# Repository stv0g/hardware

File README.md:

This repository contains several smaller PCB layouts for projects I've worked on.

For more information take a look at the README files in the particular subdirectories or search on my [blog](http://www.noteblok.net) for the projects.

## Author

Steffen Vogel <post@steffenvogel.de>

## License

All these files are released if not otherwise noted under the GNU General Public License:

Copyright (C) 2014 Steffen Vogel

This program is free software: you can redistribute it and/or modify
it under the terms of the GNU General Public License as published by
the Free Software Foundation, either version 3 of the License, or
(at your option) any later version.

This program is distributed in the hope that it will be useful,
but WITHOUT ANY WARRANTY; without even the implied warranty of
MERCHANTABILITY or FITNESS FOR A PARTICULAR PURPOSE.  See the
GNU General Public License for more details.

You should have received a copy of the GNU General Public License
along with this program.  If not, see <http://www.gnu.org/licenses/>.

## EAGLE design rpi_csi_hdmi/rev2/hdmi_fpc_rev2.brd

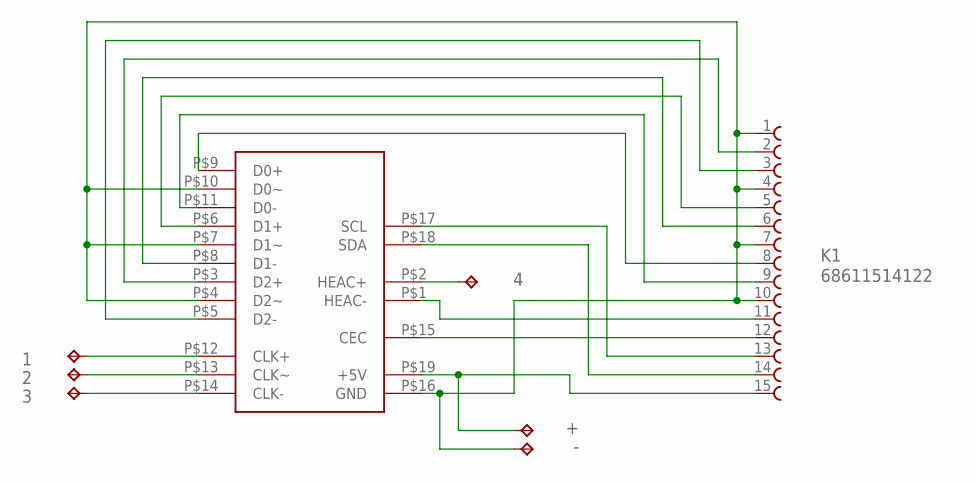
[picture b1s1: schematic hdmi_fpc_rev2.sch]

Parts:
1, 2, 3, 4: TPPAD1-13; P1-13
+: TPPAD1-13; P1-13
-: TPPAD1-13; P1-13
K1: 68611514122
U$1: HDMI_MICRO; MICRO_HDMI

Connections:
GND: -.TP, K1.1, K1.4, K1.7, K1.10, U$1.P$4 (D2~), U$1.P$7 (D1~), U$1.P$10 (D0~), U$1.P$16 (GND)
unnamed: K1.6, U$1.P$8 (D1-)
unnamed: 1.TP, U$1.P$12 (CLK+)
unnamed: K1.5, U$1.P$6 (D1+)
unnamed: K1.3, U$1.P$5 (D2-)
unnamed: K1.11, U$1.P$1 (HEAC-)
unnamed: K1.2, U$1.P$3 (D2+)
unnamed: K1.8, U$1.P$9 (D0+)
unnamed: 2.TP, U$1.P$13 (CLK~)
unnamed: K1.9, U$1.P$11 (D0-)
unnamed: K1.13, U$1.P$17 (SCL)
unnamed: K1.14, U$1.P$18 (SDA)
unnamed: +.TP, K1.15, U$1.P$19 (+5V)
unnamed: K1.12, U$1.P$15 (CEC)
unnamed: 3.TP, U$1.P$14 (CLK-)
unnamed: 4.TP, U$1.P$2 (HEAC+)

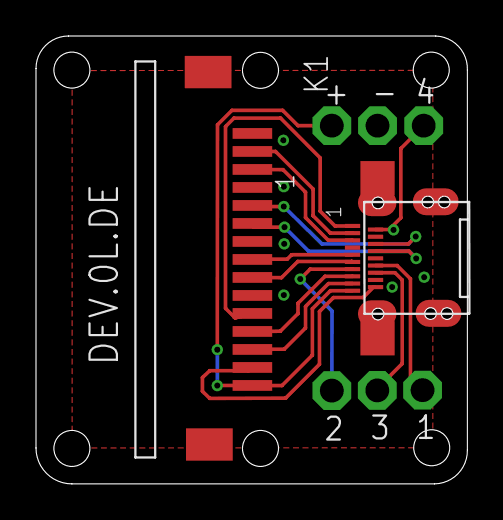
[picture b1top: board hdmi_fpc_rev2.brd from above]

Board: 2 copper layers, 24.0 x 24.9 mm, 8 parts (0 on the bottom side), 16 nets.

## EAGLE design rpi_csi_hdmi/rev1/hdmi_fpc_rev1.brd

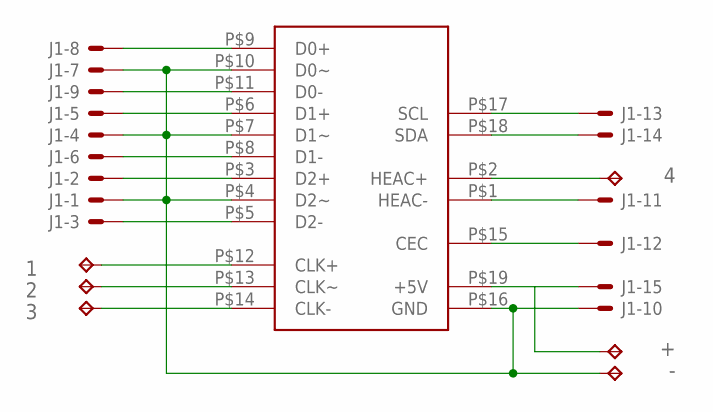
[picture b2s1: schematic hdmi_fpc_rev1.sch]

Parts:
1, 2, 3, 4: TPPAD1-13; P1-13
+: TPPAD1-13; P1-13
-: TPPAD1-13; P1-13
J1: XF2L-1535-1
U$1: HDMI_MICRO; MICRO_HDMI

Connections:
GND: -.TP, J1.1 (MSV), J1.4 (MS), J1.7 (MS), J1.10 (MS), U$1.P$4 (D2~), U$1.P$7 (D1~), U$1.P$10 (D0~), U$1.P$16 (GND)
unnamed: J1.6 (MS), U$1.P$8 (D1-)
unnamed: 1.TP, U$1.P$12 (CLK+)
unnamed: J1.5 (MS), U$1.P$6 (D1+)
unnamed: J1.3 (MS), U$1.P$5 (D2-)
unnamed: J1.11 (MS), U$1.P$1 (HEAC-)
unnamed: J1.2 (MS), U$1.P$3 (D2+)
unnamed: J1.8 (MS), U$1.P$9 (D0+)
unnamed: 2.TP, U$1.P$13 (CLK~)
unnamed: J1.9 (MS), U$1.P$11 (D0-)
unnamed: J1.13 (MS), U$1.P$17 (SCL)
unnamed: J1.14 (MS), U$1.P$18 (SDA)
unnamed: +.TP, J1.15 (MS), U$1.P$19 (+5V)
unnamed: J1.12 (MS), U$1.P$15 (CEC)
unnamed: 3.TP, U$1.P$14 (CLK-)
unnamed: 4.TP, U$1.P$2 (HEAC+)

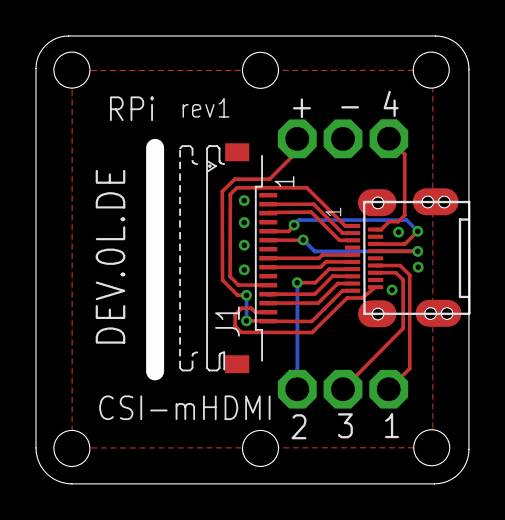
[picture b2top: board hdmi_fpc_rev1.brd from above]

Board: 2 copper layers, 23.1 x 23.9 mm, 8 parts (0 on the bottom side), 16 nets.

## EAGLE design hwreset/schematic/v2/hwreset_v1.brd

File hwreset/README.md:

# HWreset

'HWreset' is a little ATmega8 microcontroller which uses the V-USB software stack to connect to your PC.
Its equipped with two low voltage singaling relays to emulate your power and reset switches on a secondary SUT (system under test).

I use this little tool to speed up my compile & debug cycle for x86 os development with [MetalSVM] (http://www.lfbs.rwth-aachen.de/content/765)

## Hardware

You might want to use an existing [USBasp] (http://www.fischl.de/usbasp/) AVR Programmer and reflash it with the provided firmware. The USBasp is also based on the V-USB stack and has pretty much everything we need conserning the hardware.
The firmware is compatible with the USBasp pin assignments.

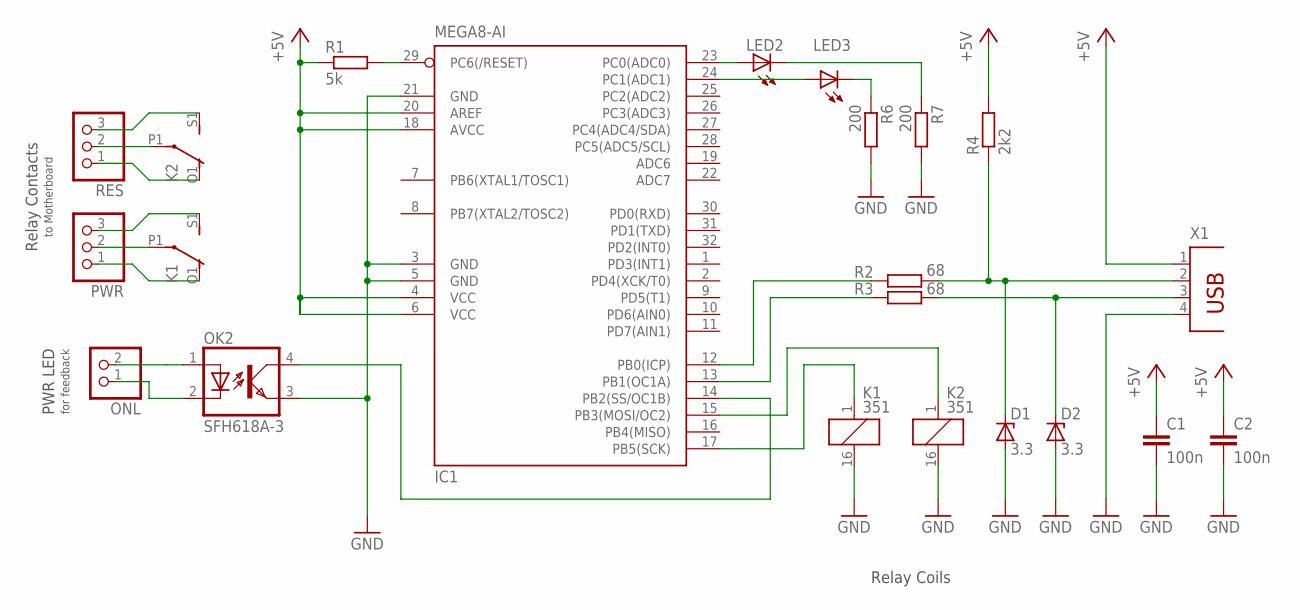
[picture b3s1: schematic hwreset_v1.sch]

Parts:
C1, C2: 100n; C025-025X050
D1, D2: 3.3; ZDIO-2.5
IC1: MEGA8-AI; TQFP32-08
K1, K2: 351
LED2, LED3: LED3MM
OK2: SFH618A-3; DIP4
ONL: PINHD-1X2; 1X02
PWR: PINHD-1X3; 1X03
R1: 5k; 0204V
R2, R3: 68; 0204V
R4: 2k2; 0204V
R6, R7: 200; 0204V
RES: PINHD-1X3; 1X03
X1: PN87520

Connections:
+5V: C1.1, C2.1, IC1.4 (VCC), IC1.6 (VCC), IC1.18 (AVCC), IC1.20 (AREF), R1.1, R4.2, X1.1
GND: C1.2, C2.2, D1.A, IC1.3 (GND), IC1.5 (GND), IC1.21 (GND), K1.16 (2), K2.16 (2), OK2.3 (EMIT), R6.2, R7.2, X1.4
unnamed: IC1.29 (PC6(/RESET)), R1.2
unnamed: IC1.17 (PB5(SCK)), K1.1
unnamed: K2.P1, RES.2
unnamed: IC1.12 (PB0(ICP)), R2.1
unnamed: IC1.13 (PB1(OC1A)), R3.1
unnamed: K1.P1, PWR.2
unnamed: D1.C, R2.2, R4.1, X1.2
unnamed: D2.C, R3.2, X1.3
unnamed: K1.O1 (O), PWR.1
unnamed: K1.S1 (S), PWR.3
unnamed: K2.O1 (O), RES.1
unnamed: K2.S1 (S), RES.3
unnamed: OK2.1 (A), ONL.2
unnamed: OK2.2 (C), ONL.1
unnamed: IC1.14 (PB2(SS/OC1B)), OK2.4 (COL)
unnamed: IC1.23 (PC0(ADC0)), LED2.A
unnamed: IC1.15 (PB3(MOSI/OC2)), K2.1
unnamed: IC1.24 (PC1(ADC1)), LED3.A
unnamed: LED2.K (C), R7.1
unnamed: LED3.K (C), R6.1

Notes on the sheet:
Relay Coils
Relay Contacts
to Motherboard
PWR LED
for feedback

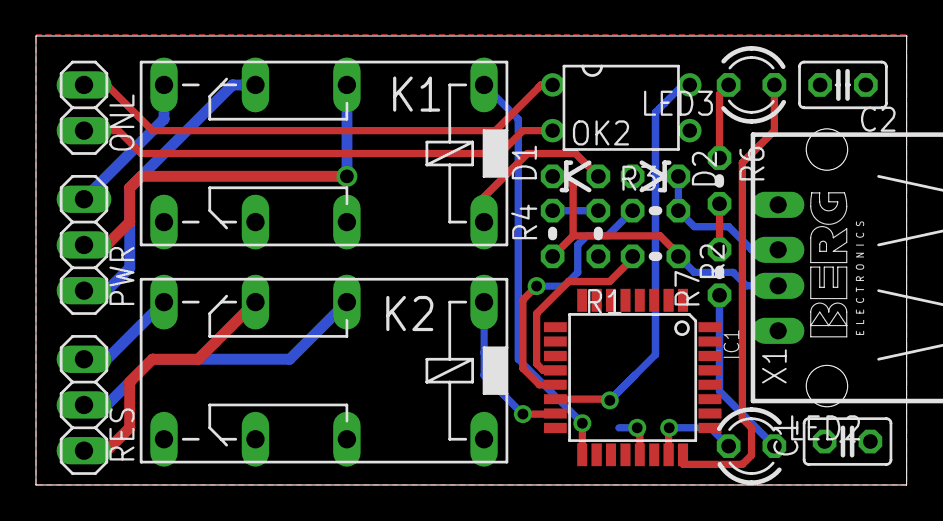
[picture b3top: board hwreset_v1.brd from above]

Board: 2 copper layers, 48.4 x 24.9 mm, 20 parts (0 on the bottom side), 22 nets.

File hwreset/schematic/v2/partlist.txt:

Partlist

Exported from untitled.sch at 18.01.14 01:03

EAGLE Version 6.1.0 Copyright (c) 1988-2012 CadSoft

Assembly variant: 

Part     Value          Device            Package      Library     Sheet

C1       100n           C-EU025-025X050   C025-025X050 rcl         1
C2       100n           C-EU025-025X050   C025-025X050 rcl         1
D1       3.3            ZENER-DIODEZD-2.5 ZDIO-2.5     diode       1
D2       3.3            ZENER-DIODEZD-2.5 ZDIO-2.5     diode       1
IC1      TINY22P        TINY22P           DIL08        atmel       1
K1       351            351               351          relay       1
K2       351            351               351          relay       1
LED1                    LED3MM            LED3MM       led         1
OK2      SFH618A-3      SFH618A-3         DIP4         optocoupler 1
ONL                     PINHD-1X2         1X02         pinhead     1
PWR                     PINHD-1X3         1X03         pinhead     1
R1       5k             R-EU_0204/2V      0204V        rcl         1
R2       68             R-EU_0204/2V      0204V        rcl         1
R3       68             R-EU_0204/2V      0204V        rcl         1
R4       2k2            R-EU_0204/2V      0204V        rcl         1
R5       200            R-EU_0204/2V      0204V        rcl         1
RES                     PINHD-1X3         1X03         pinhead     1
X1                      PN87520           PN87520      con-berg    1

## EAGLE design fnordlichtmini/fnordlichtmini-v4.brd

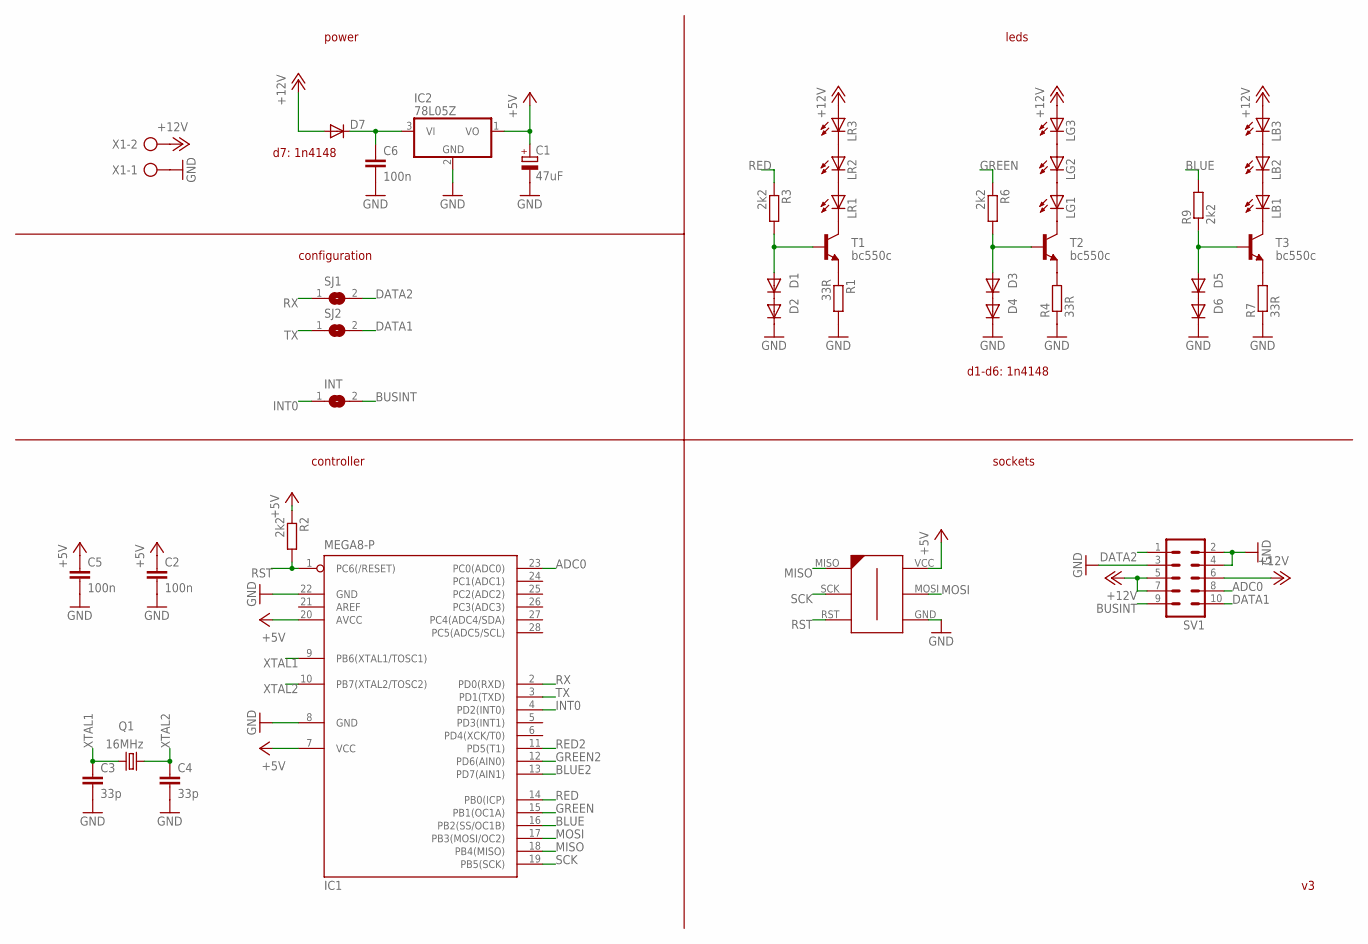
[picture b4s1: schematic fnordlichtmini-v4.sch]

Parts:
C1: 47uF; E2-5
C2, C5, C6: 100n; C025-024X044
C3, C4: 33p; C025-024X044
D1, D2, D3, D4, D5, D6, D7: DIODE-D-2.5; D-2.5
IC1: MEGA8-P; DIL28-3
IC2: 78L05Z; TO92
INT: SJ
LB1, LB2, LB3: LED5MM
LG1, LG2, LG3: LED5MM
LR1, LR2, LR3: LED5MM
Q1: 16MHz; HC49U-V
R1, R4, R7: 33R; 0204V
R2, R3, R6, R9: 2k2; 0204V
SJ1, SJ2: SJ
SV1: MA05-2
T1, T2, T3: bc550c; TO92
U$1: AVR-ISP-6-EDGE; 6PAD_ISP
X1: AK500/2

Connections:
+5V: C1.+, C2.1, C5.1, IC1.7 (VCC), IC1.20 (AVCC), IC2.1 (VO), R2.1, U$1.VCC
+12V: D7.A, LB3.A, LG3.A, LR3.A, SV1.5, SV1.6, SV1.7, X1.2
ADC0: IC1.23 (PC0(ADC0)), SV1.8
BLUE: IC1.16 (PB2(SS/OC1B)), R9.2
BLUE2: IC1.13 (PD7(AIN1))
BUSINT: INT.2, SV1.9
DATA1: SJ2.2, SV1.10
DATA2: SJ1.2, SV1.1
GND: C1.-, C2.2, C3.2, C4.2, C5.2, C6.2, D2.C, D4.C, D6.C, IC1.8 (GND), IC1.22 (GND), IC2.2 (GND), R1.2, R4.1, R7.1, SV1.2, SV1.3, SV1.4, U$1.GND, X1.1
GREEN: IC1.15 (PB1(OC1A)), R6.1
GREEN2: IC1.12 (PD6(AIN0))
INT0: IC1.4 (PD2(INT0)), INT.1
MISO: IC1.18 (PB4(MISO)), U$1.MISO
MOSI: IC1.17 (PB3(MOSI/OC2)), U$1.MOSI
unnamed: LR2.A, LR3.K (C)
unnamed: LR1.A, LR2.K (C)
unnamed: LR1.K (C), T1.3 (C)
unnamed: D1.C, D2.A
unnamed: R1.1, T1.1 (E)
unnamed: D1.A, R3.2, T1.2 (B)
unnamed: LG2.A, LG3.K (C)
unnamed: LG1.A, LG2.K (C)
unnamed: LG1.K (C), T2.3 (C)
unnamed: D3.C, D4.A
unnamed: R4.2, T2.1 (E)
unnamed: D3.A, R6.2, T2.2 (B)
unnamed: LB2.A, LB3.K (C)
unnamed: LB1.A, LB2.K (C)
unnamed: LB1.K (C), T3.3 (C)
unnamed: D5.C, D6.A
unnamed: R7.2, T3.1 (E)
unnamed: D5.A, R9.1, T3.2 (B)
unnamed: C6.1, D7.C, IC2.3 (VI)
RED: IC1.14 (PB0(ICP)), R3.1
RED2: IC1.11 (PD5(T1))
RST: IC1.1 (PC6(/RESET)), R2.2, U$1.RST
RX: IC1.2 (PD0(RXD)), SJ1.1
SCK: IC1.19 (PB5(SCK)), U$1.SCK
TX: IC1.3 (PD1(TXD)), SJ2.1
XTAL1: C3.1, IC1.9 (PB6(XTAL1/TOSC1)), Q1.1
XTAL2: C4.1, IC1.10 (PB7(XTAL2/TOSC2)), Q1.2

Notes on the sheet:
leds
configuration
controller
sockets
power
d7: 1n4148
d1-d6: 1n4148

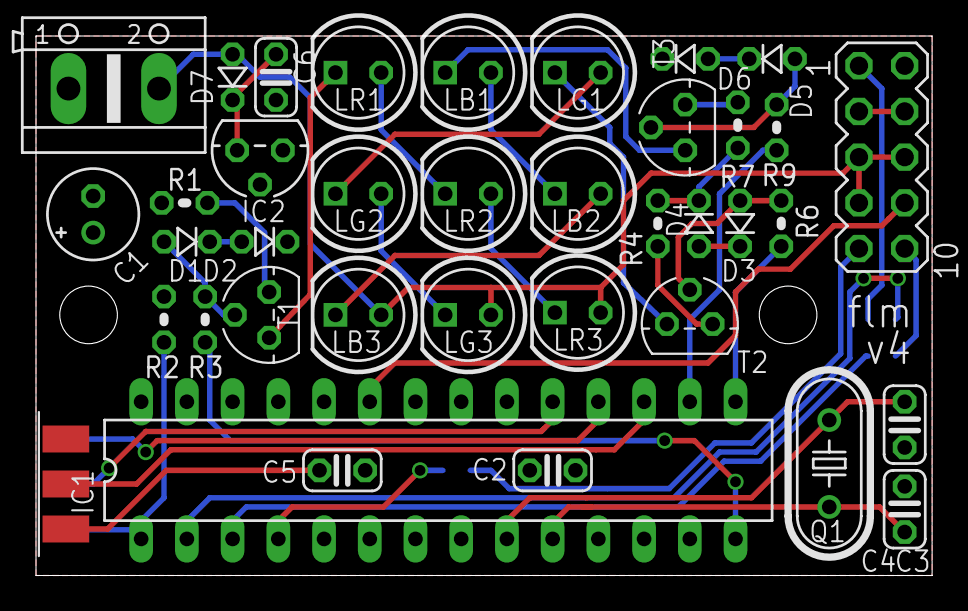
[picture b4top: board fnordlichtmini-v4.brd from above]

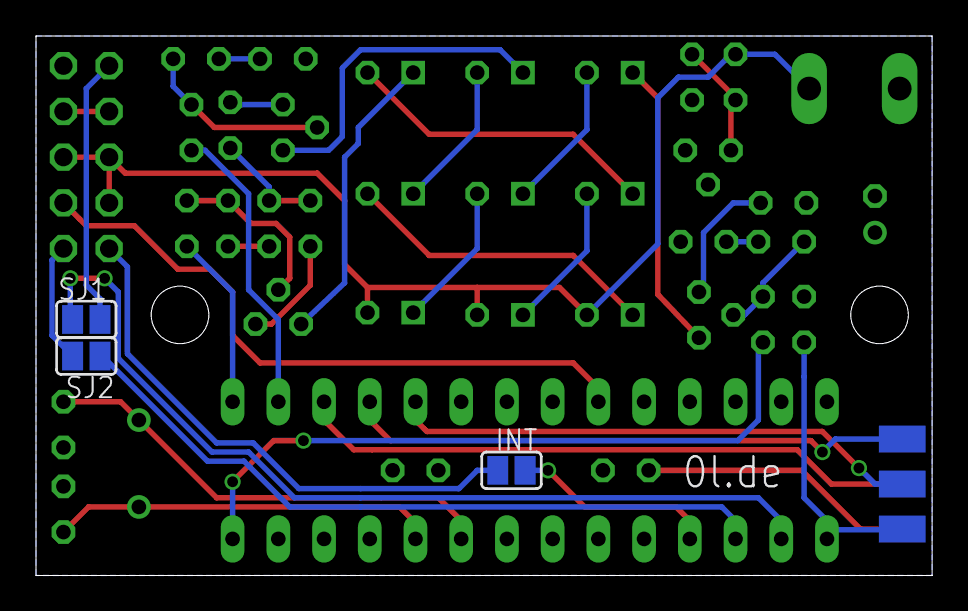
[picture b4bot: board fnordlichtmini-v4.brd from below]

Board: 2 copper layers, 49.8 x 30.0 mm, 41 parts (3 on the bottom side), 38 nets.

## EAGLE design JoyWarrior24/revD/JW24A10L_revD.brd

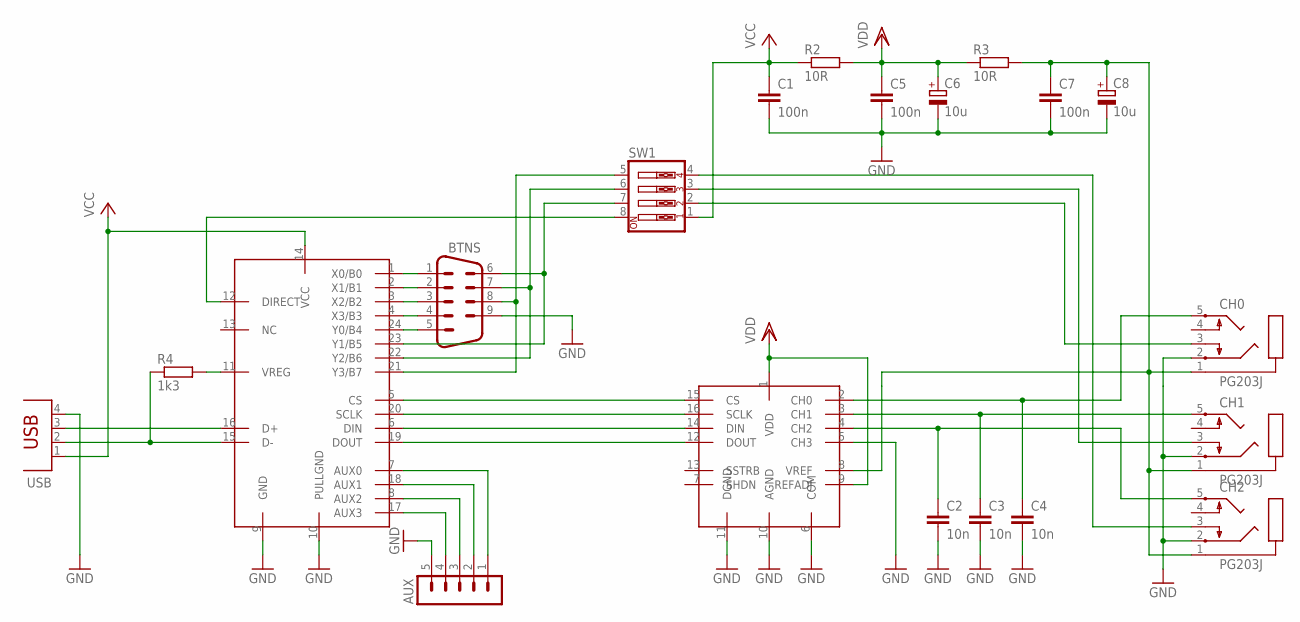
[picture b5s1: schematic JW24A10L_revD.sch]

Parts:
AUX: MA05-1
BTNS: M09H
C1, C5, C7: 100n; C025-025X050
C2, C3, C4: 10n; C025-025X050
C6, C8: 10u; E2-5
CH0, CH1, CH2: PG203J
R2, R3: 10R; 0207/2V
R4: 1k3; 0207/2V
SW1: SW_DIP-4; EDG-04
U$1: MAX1249; DIL16
U$2: JW24A10L; DIL24-3
USB: PN61729

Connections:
AUX0: AUX.1, U$2.7 (AUX0)
AUX1: AUX.2, U$2.18 (AUX1)
AUX2: AUX.3, U$2.8 (AUX2)
AUX3: AUX.4, U$2.17 (AUX3)
CH0: C4.1, CH0.5, U$1.2 (CH0)
CH1: C3.1, CH1.5, U$1.3 (CH1)
CH2: C2.1, CH2.5, U$1.4 (CH2)
CH+: C7.1, C8.+, CH0.1, CH1.1, CH2.1, R3.2, U$1.8 (VREF)
D+: U$2.16 (D+), USB.3
D-: R4.1, U$2.15 (D-), USB.2
GND: AUX.5, BTNS.9, C1.2, C2.2, C3.2, C4.2, C5.2, C6.-, C7.2, C8.-, CH0.2, CH1.2, CH2.2, U$1.5 (CH3), U$1.6 (COM), U$1.10 (AGND), U$1.11 (DGND), U$2.9 (GND), U$2.10 (PULLGND), USB.4
unnamed: U$1.15 (CS), U$2.5 (CS)
unnamed: U$1.16 (SCLK), U$2.20 (SCLK)
unnamed: U$1.14 (DIN), U$2.6 (DIN)
unnamed: U$1.12 (DOUT), U$2.19 (DOUT)
unnamed: BTNS.1, U$2.1 (X0/B0)
unnamed: R4.2, U$2.11 (VREG)
unnamed: BTNS.2, U$2.2 (X1/B1)
unnamed: BTNS.3, U$2.3 (X2/B2)
unnamed: BTNS.4, U$2.4 (X3/B3)
unnamed: BTNS.5, U$2.24 (Y0/B4)
unnamed: BTNS.6, SW1.7, U$2.23 (Y1/B5)
unnamed: BTNS.7, SW1.6, U$2.22 (Y2/B6)
unnamed: BTNS.8, SW1.5, U$2.21 (Y3/B7)
unnamed: SW1.8, U$2.12 (DIRECT)
STECK0: CH0.3, SW1.2
STECK1: CH1.3, SW1.3
STECK2: CH2.3, SW1.4
VCC: C1.1, R2.1, SW1.1, U$2.14 (VCC), USB.1
VDD: C5.1, C6.+, R2.2, R3.1, U$1.1 (VDD), U$1.9 (REFADJ)

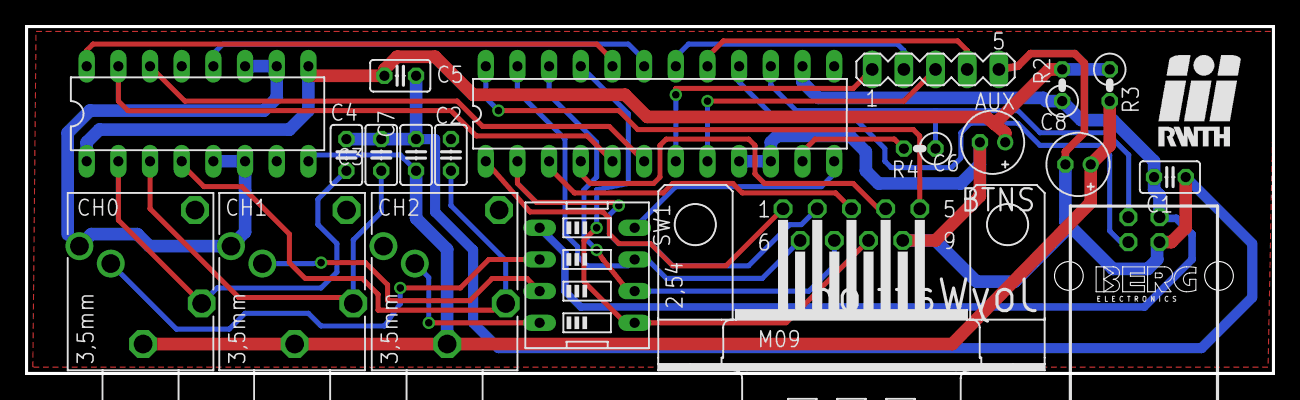
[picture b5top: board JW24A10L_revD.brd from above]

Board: 2 copper layers, 100.0 x 27.8 mm, 20 parts (0 on the bottom side), 30 nets.

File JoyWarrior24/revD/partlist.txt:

Partlist

Exported from JW24A10L_revD.sch at 04.01.14 19:11

EAGLE Version 6.1.0 Copyright (c) 1988-2012 CadSoft

Assembly variant: 

Part     Value          Device          Package      Library        Sheet

AUX                     MA05-1          MA05-1       con-lstb       1
BTNS                    M09H            M09H         con-subd       1
C1       100n           C-EU025-025X050 C025-025X050 rcl            1
C2       10n            C-EU025-025X050 C025-025X050 rcl            1
C3       10n            C-EU025-025X050 C025-025X050 rcl            1
C4       10n            C-EU025-025X050 C025-025X050 rcl            1
C5       100n           C-EU025-025X050 C025-025X050 rcl            1
C6       10u            CPOL-EUE2-5     E2-5         rcl            1
C7       100n           C-EU025-025X050 C025-025X050 rcl            1
C8       10u            CPOL-EUE2-5     E2-5         rcl            1
CH0      PG203J         PG203J          PG203J       con-hirschmann 1
CH1      PG203J         PG203J          PG203J       con-hirschmann 1
CH2      PG203J         PG203J          PG203J       con-hirschmann 1
R2       10R            R-EU_0207/2V    0207/2V      rcl            1
R3       10R            R-EU_0207/2V    0207/2V      rcl            1
R4       1k3            R-EU_0207/2V    0207/2V      rcl            1
SW1                     SW_DIP-4        EDG-04       special        1
U$1      MAX1249        MAX1249         DIL16        eigene         1
U$2      JW24A10L       JW24A10L        DIL24-3      eigene         1
USB                     PN61729         PN61729      con-berg       1

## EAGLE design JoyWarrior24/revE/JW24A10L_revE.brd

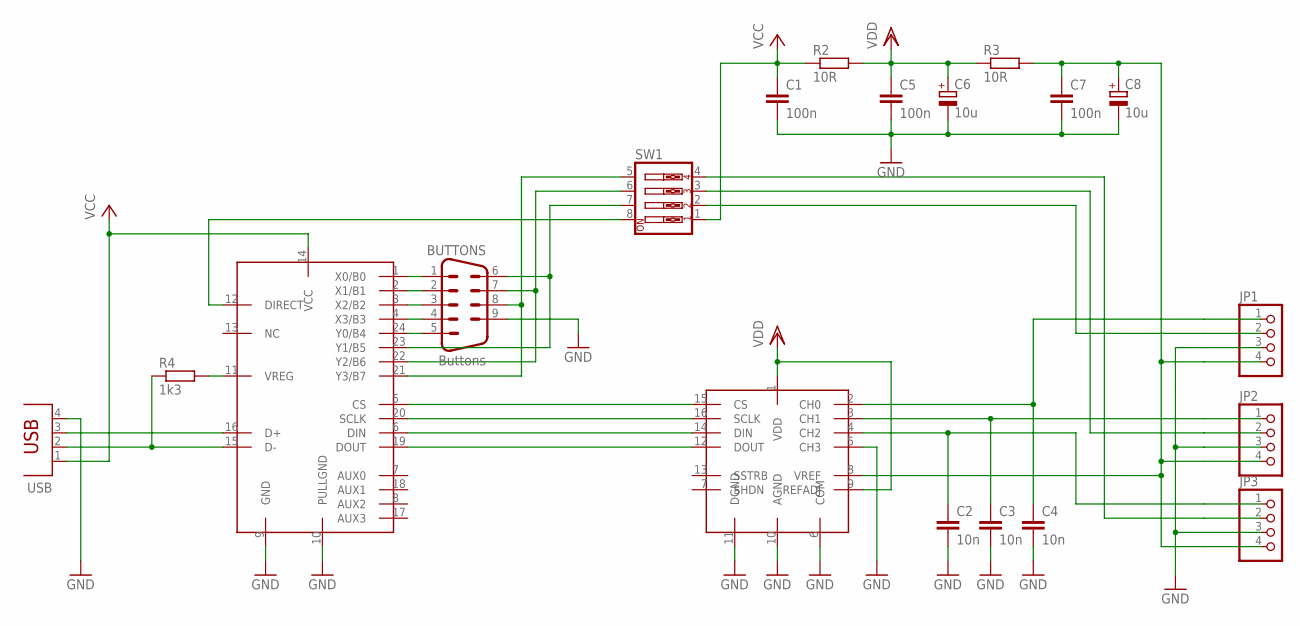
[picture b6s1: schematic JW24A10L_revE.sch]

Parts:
BUTTONS: Buttons; M09H
C1, C5, C7: 100n; C025-025X050
C2, C3, C4: 10n; C025-025X050
C6, C8: 10u; E2-5
JP1, JP2, JP3: PINHD-1X4; 1X04
R2, R3: 10R; 0207/2V
R4: 1k3; 0207/2V
SW1: SW_DIP-4; EDG-04
U$1: MAX1249; DIL16
U$2: JW24A10L; DIL24-3
USB: PN61729

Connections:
CH0: C4.1, JP1.1, U$1.2 (CH0)
CH1: C3.1, JP2.1, U$1.3 (CH1)
CH2: C2.1, JP3.1, U$1.4 (CH2)
CH+: C7.1, C8.+, JP1.4, JP2.4, JP3.4, R3.2, U$1.8 (VREF)
D+: U$2.16 (D+), USB.3
D-: R4.1, U$2.15 (D-), USB.2
GND: BUTTONS.9, C1.2, C2.2, C3.2, C4.2, C5.2, C6.-, C7.2, C8.-, JP1.3, JP2.3, JP3.3, U$1.5 (CH3), U$1.6 (COM), U$1.10 (AGND), U$1.11 (DGND), U$2.9 (GND), U$2.10 (PULLGND), USB.4
unnamed: U$1.15 (CS), U$2.5 (CS)
unnamed: U$1.16 (SCLK), U$2.20 (SCLK)
unnamed: U$1.14 (DIN), U$2.6 (DIN)
unnamed: U$1.12 (DOUT), U$2.19 (DOUT)
unnamed: BUTTONS.1, U$2.1 (X0/B0)
unnamed: R4.2, U$2.11 (VREG)
unnamed: BUTTONS.2, U$2.2 (X1/B1)
unnamed: BUTTONS.3, U$2.3 (X2/B2)
unnamed: BUTTONS.4, U$2.4 (X3/B3)
unnamed: BUTTONS.5, U$2.24 (Y0/B4)
unnamed: BUTTONS.6, SW1.7, U$2.23 (Y1/B5)
unnamed: BUTTONS.7, SW1.6, U$2.22 (Y2/B6)
unnamed: BUTTONS.8, SW1.5, U$2.21 (Y3/B7)
unnamed: SW1.8, U$2.12 (DIRECT)
STECK0: JP1.2, SW1.2
STECK1: JP2.2, SW1.3
STECK2: JP3.2, SW1.4
VCC: C1.1, R2.1, SW1.1, U$2.14 (VCC), USB.1
VDD: C5.1, C6.+, R2.2, R3.1, U$1.1 (VDD), U$1.9 (REFADJ)

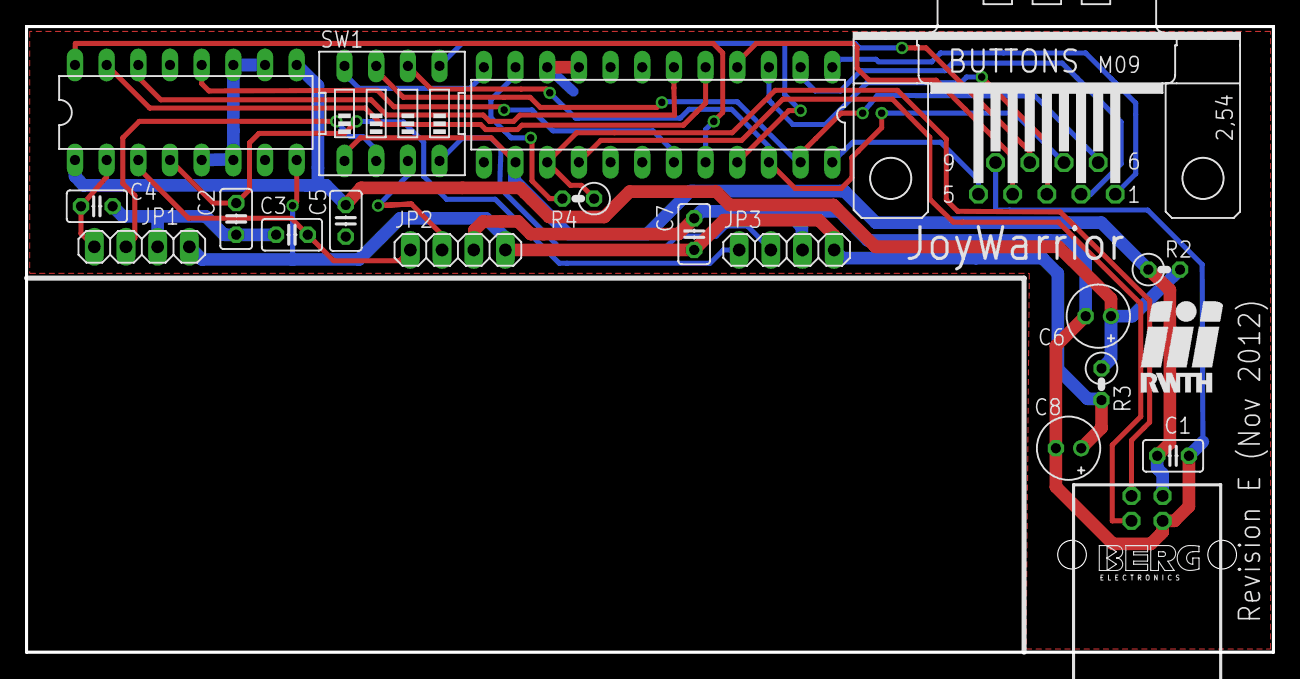
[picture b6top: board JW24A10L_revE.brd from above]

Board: 2 copper layers, 100.0 x 50.2 mm, 19 parts (0 on the bottom side), 26 nets.

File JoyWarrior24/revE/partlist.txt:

Partlist

Exported from JW24A10L_revE.sch at 04.01.14 19:11

EAGLE Version 6.1.0 Copyright (c) 1988-2012 CadSoft

Assembly variant: 

Part     Value          Device          Package      Library  Sheet

BUTTONS  Buttons        M09H            M09H         con-subd 1
C1       100n           C-EU025-025X050 C025-025X050 rcl      1
C2       10n            C-EU025-025X050 C025-025X050 rcl      1
C3       10n            C-EU025-025X050 C025-025X050 rcl      1
C4       10n            C-EU025-025X050 C025-025X050 rcl      1
C5       100n           C-EU025-025X050 C025-025X050 rcl      1
C6       10u            CPOL-EUE2-5     E2-5         rcl      1
C7       100n           C-EU025-025X050 C025-025X050 rcl      1
C8       10u            CPOL-EUE2-5     E2-5         rcl      1
JP1                     PINHD-1X4       1X04         pinhead  1
JP2                     PINHD-1X4       1X04         pinhead  1
JP3                     PINHD-1X4       1X04         pinhead  1
R2       10R            R-EU_0207/2V    0207/2V      rcl      1
R3       10R            R-EU_0207/2V    0207/2V      rcl      1
R4       1k3            R-EU_0207/2V    0207/2V      rcl      1
SW1                     SW_DIP-4        EDG-04       special  1
U$1      MAX1249        MAX1249         DIL16        eigene   1
U$2      JW24A10L       JW24A10L        DIL24-3      eigene   1
USB                     PN61729         PN61729      con-berg 1

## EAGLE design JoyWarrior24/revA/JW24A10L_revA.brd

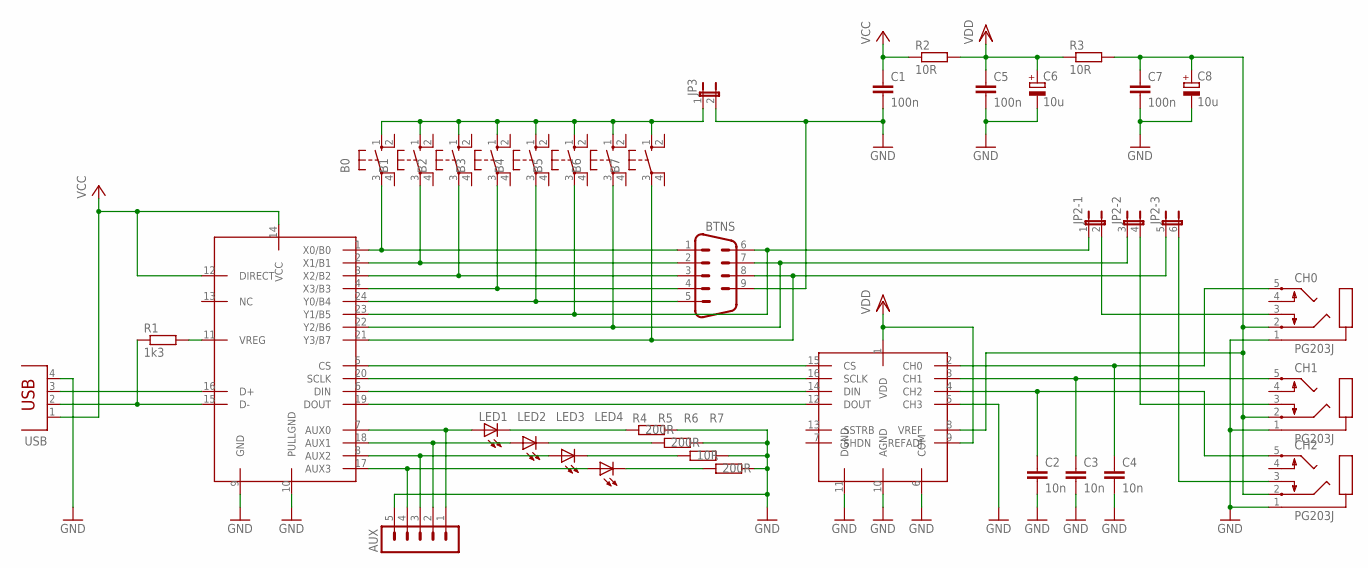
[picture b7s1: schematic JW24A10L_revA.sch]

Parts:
AUX: MA05-1
B0, B1: 10-XX; B3F-10XX
B2, B3, B4, B5, B6, B7: 10-XX; B3F-10XX; MPN B3F-1000
BTNS: M09HP
C1, C5, C7: 100n; C025-025X050
C2, C3, C4: 10n; C025-025X050
C6, C8: 10u; E2-5
CH0, CH1, CH2: PG203J
JP2: JP3QE; JP3Q
JP3: JP1E; JP1
LED1, LED2, LED3, LED4: LED3MM
R1: 1k3; 0204/7
R2, R3, R6: 10R; 0204/7
R4, R5, R7: 200R; 0204/7
U$1: MAX1249; DIL16
U$2: JW24A10L; DIL24-3
USB: PN61729

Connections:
AUX0: AUX.1, LED1.A, U$2.7 (AUX0)
AUX1: AUX.2, LED2.A, U$2.18 (AUX1)
AUX2: AUX.3, LED3.A, U$2.8 (AUX2)
AUX3: AUX.4, LED4.A, U$2.17 (AUX3)
CH1: C4.1, CH0.5, U$1.2 (CH0)
CH2: CH2.3, JP2.6 (2)
GND: AUX.5, BTNS.9, C1.2, C2.2, C3.2, C4.2, C5.2, C6.-, C7.2, C8.-, CH0.1, CH1.1, CH2.1, JP3.2, R4.2, R5.2, R6.2, R7.2, U$1.5 (CH3), U$1.6 (COM), U$1.10 (AGND), U$1.11 (DGND), U$2.9 (GND), U$2.10 (PULLGND), USB.4
unnamed: U$1.15 (CS), U$2.5 (CS)
unnamed: U$1.16 (SCLK), U$2.20 (SCLK)
unnamed: U$1.14 (DIN), U$2.6 (DIN)
unnamed: U$1.12 (DOUT), U$2.19 (DOUT)
unnamed: U$2.16 (D+), USB.3
unnamed: R1.1, U$2.15 (D-), USB.2
unnamed: B0.3, BTNS.1, U$2.1 (X0/B0)
unnamed: R1.2, U$2.11 (VREG)
unnamed: C3.1, CH1.5, U$1.3 (CH1)
unnamed: C2.1, CH2.5, U$1.4 (CH2)
unnamed: B1.3, BTNS.2, U$2.2 (X1/B1)
unnamed: B2.3, BTNS.3, U$2.3 (X2/B2)
unnamed: B3.3, BTNS.4, U$2.4 (X3/B3)
unnamed: B4.3, BTNS.5, U$2.24 (Y0/B4)
unnamed: B5.3, BTNS.6, JP2.1, U$2.23 (Y1/B5)
unnamed: B6.3, BTNS.7, JP2.3 (1), U$2.22 (Y2/B6)
unnamed: B7.3, BTNS.8, JP2.5 (1), U$2.21 (Y3/B7)
unnamed: CH1.3, JP2.4 (2)
unnamed: CH0.3, JP2.2
unnamed: C7.1, C8.+, CH0.2, CH1.2, CH2.2, R3.2, U$1.8 (VREF)
unnamed: LED1.K (C), R4.1
unnamed: LED2.K (C), R5.1
unnamed: LED3.K (C), R6.1
unnamed: LED4.K (C), R7.1
unnamed: B0.1 (S), B1.1 (S), B2.1 (S), B3.1 (S), B4.1 (S), B5.1 (S), B6.1 (S), B7.1 (S), JP3.1
VCC: C1.1, R2.1, U$2.12 (DIRECT), U$2.14 (VCC), USB.1
VDD: C5.1, C6.+, R2.2, R3.1, U$1.1 (VDD), U$1.9 (REFADJ)

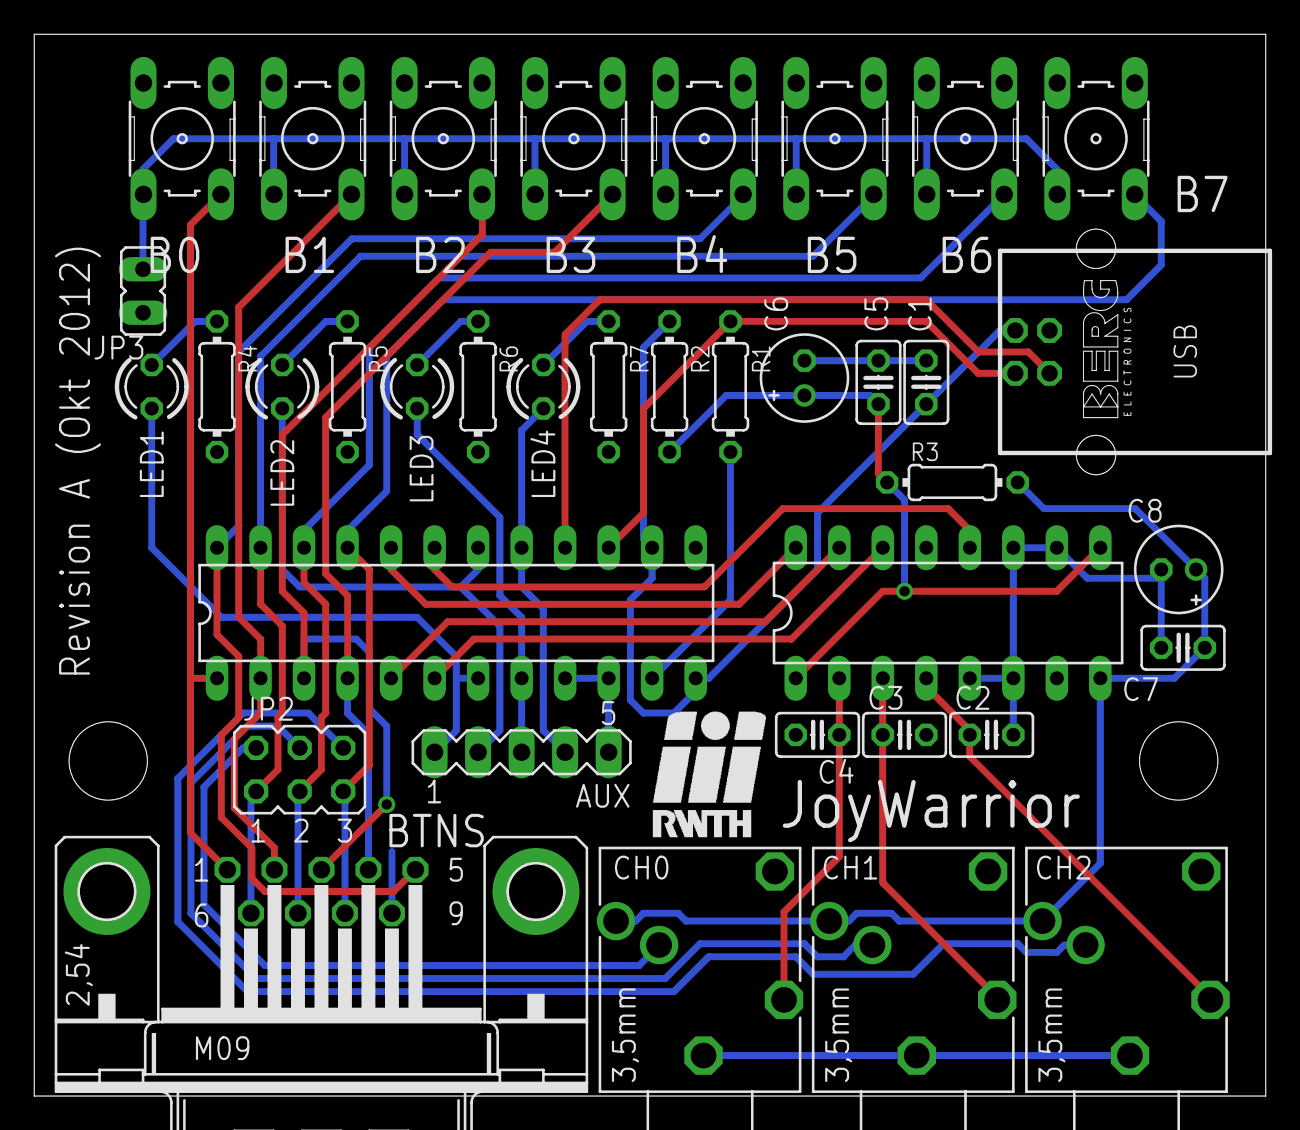
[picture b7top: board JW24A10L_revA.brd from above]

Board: 2 copper layers, 71.9 x 62.0 mm, 37 parts (0 on the bottom side), 34 nets.

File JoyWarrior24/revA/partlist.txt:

Partlist

Exported from JW24A10L_revA.sch at 04.01.14 19:08

EAGLE Version 6.1.0 Copyright (c) 1988-2012 CadSoft

Assembly variant: 

Part     Value          Device          Package      Library        Sheet

AUX                     MA05-1          MA05-1       con-lstb       1
B0                      10-XX           B3F-10XX     switch-omron   1
B1                      10-XX           B3F-10XX     switch-omron   1
B2                      10-XX           B3F-10XX     switch-omron   1
B3                      10-XX           B3F-10XX     switch-omron   1
B4                      10-XX           B3F-10XX     switch-omron   1
B5                      10-XX           B3F-10XX     switch-omron   1
B6                      10-XX           B3F-10XX     switch-omron   1
B7                      10-XX           B3F-10XX     switch-omron   1
BTNS                    M09HP           M09HP        con-subd       1
C1       100n           C-EU025-025X050 C025-025X050 rcl            1
C2       10n            C-EU025-025X050 C025-025X050 rcl            1
C3       10n            C-EU025-025X050 C025-025X050 rcl            1
C4       10n            C-EU025-025X050 C025-025X050 rcl            1
C5       100n           C-EU025-025X050 C025-025X050 rcl            1
C6       10u            CPOL-EUE2-5     E2-5         rcl            1
C7       100n           C-EU025-025X050 C025-025X050 rcl            1
C8       10u            CPOL-EUE2-5     E2-5         rcl            1
CH0      PG203J         PG203J          PG203J       con-hirschmann 1
CH1      PG203J         PG203J          PG203J       con-hirschmann 1
CH2      PG203J         PG203J          PG203J       con-hirschmann 1
JP2                     JP3QE           JP3Q         jumper         1
JP3                     JP1E            JP1          jumper         1
LED1                    LED3MM          LED3MM       led            1
LED2                    LED3MM          LED3MM       led            1
LED3                    LED3MM          LED3MM       led            1
LED4                    LED3MM          LED3MM       led            1
R1       1k3            R-EU_0204/7     0204/7       rcl            1
R2       10R            R-EU_0204/7     0204/7       rcl            1
R3       10R            R-EU_0204/7     0204/7       rcl            1
R4       200R           R-EU_0204/7     0204/7       rcl            1
R5       200R           R-EU_0204/7     0204/7       rcl            1
R6       10R            R-EU_0204/7     0204/7       rcl            1
R7       200R           R-EU_0204/7     0204/7       rcl            1
U$1      MAX1249        MAX1249         DIL16        eigene         1
U$2      JW24A10L       JW24A10L        DIL24-3      eigene         1
USB                     PN61729         PN61729      con-berg       1

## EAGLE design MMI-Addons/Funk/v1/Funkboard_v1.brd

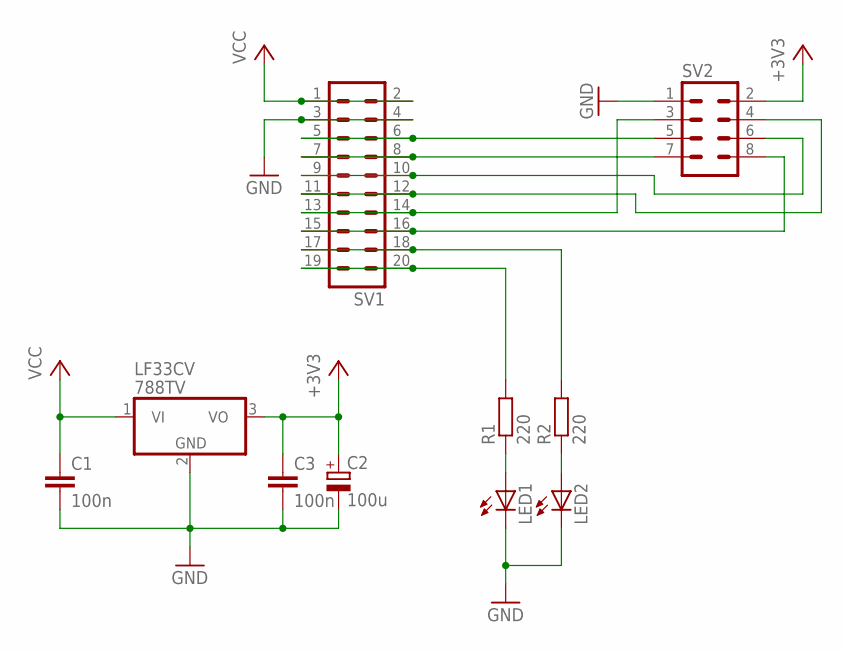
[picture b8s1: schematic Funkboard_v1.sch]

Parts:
C1, C3: 100n; C025-025X050
C2: 100u; E2,5-6
LED1, LED2: LED3MM
LF33CV: 788TV; TO220V
R1, R2: 220; 0204V
SV1: MA10-2W
SV2: MA04-2

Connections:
+3V3: C2.+, C3.1, LF33CV.3 (VO), SV2.2
GND: C1.2, C2.-, C3.2, LED1.K (C), LED2.K (C), LF33CV.2 (GND), SV1.3, SV1.4, SV2.1
unnamed: LED1.A, R1.1
unnamed: LED2.A, R2.1
unnamed: SV1.5, SV1.6, SV2.5
unnamed: SV1.7, SV1.8, SV2.7
unnamed: SV1.9, SV1.10, SV2.6
unnamed: SV1.11, SV1.12, SV2.4
unnamed: SV1.13, SV1.14, SV2.3
unnamed: SV1.15, SV1.16, SV2.8
unnamed: R2.2, SV1.17, SV1.18
unnamed: R1.2, SV1.19, SV1.20
VCC: C1.1, LF33CV.1 (VI), SV1.1, SV1.2

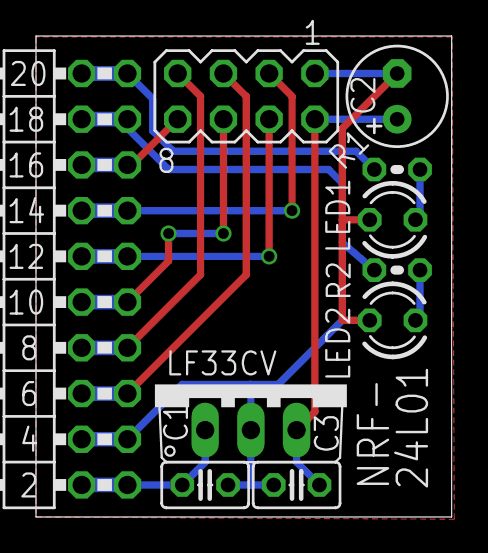
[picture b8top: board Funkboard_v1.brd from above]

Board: 2 copper layers, 23.1 x 26.7 mm, 10 parts (0 on the bottom side), 13 nets.

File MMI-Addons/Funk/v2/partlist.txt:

Partlist

Exported from Funkboard_v2.sch at 04.01.14 20:28

EAGLE Version 6.1.0 Copyright (c) 1988-2012 CadSoft

Assembly variant: 

Part     Value          Device          Package      Library  Sheet

C1       100n           C-EU025-025X050 C025-025X050 rcl      1
C2       100u           CPOL-EUE2.5-6   E2,5-6       rcl      1
C3       100n           C-EU025-025X050 C025-025X050 rcl      1
IC1      LP2950Z        LP2950Z         TO92         linear   1
LED1                    LED3MM          LED3MM       led      1
LED2                    LED3MM          LED3MM       led      1
R1       220            R-EU_0204/2V    0204V        rcl      1
R2       220            R-EU_0204/2V    0204V        rcl      1
SV1                     MA10-2W         MA10-2W      con-lstb 1
SV2                     MA04-2          MA04-2       con-lstb 1

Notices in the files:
parts and their libraries:
EagleLibrary_Wuerth_Elektronik_eiCan_FPC: Copyright: Würth Elektronik
